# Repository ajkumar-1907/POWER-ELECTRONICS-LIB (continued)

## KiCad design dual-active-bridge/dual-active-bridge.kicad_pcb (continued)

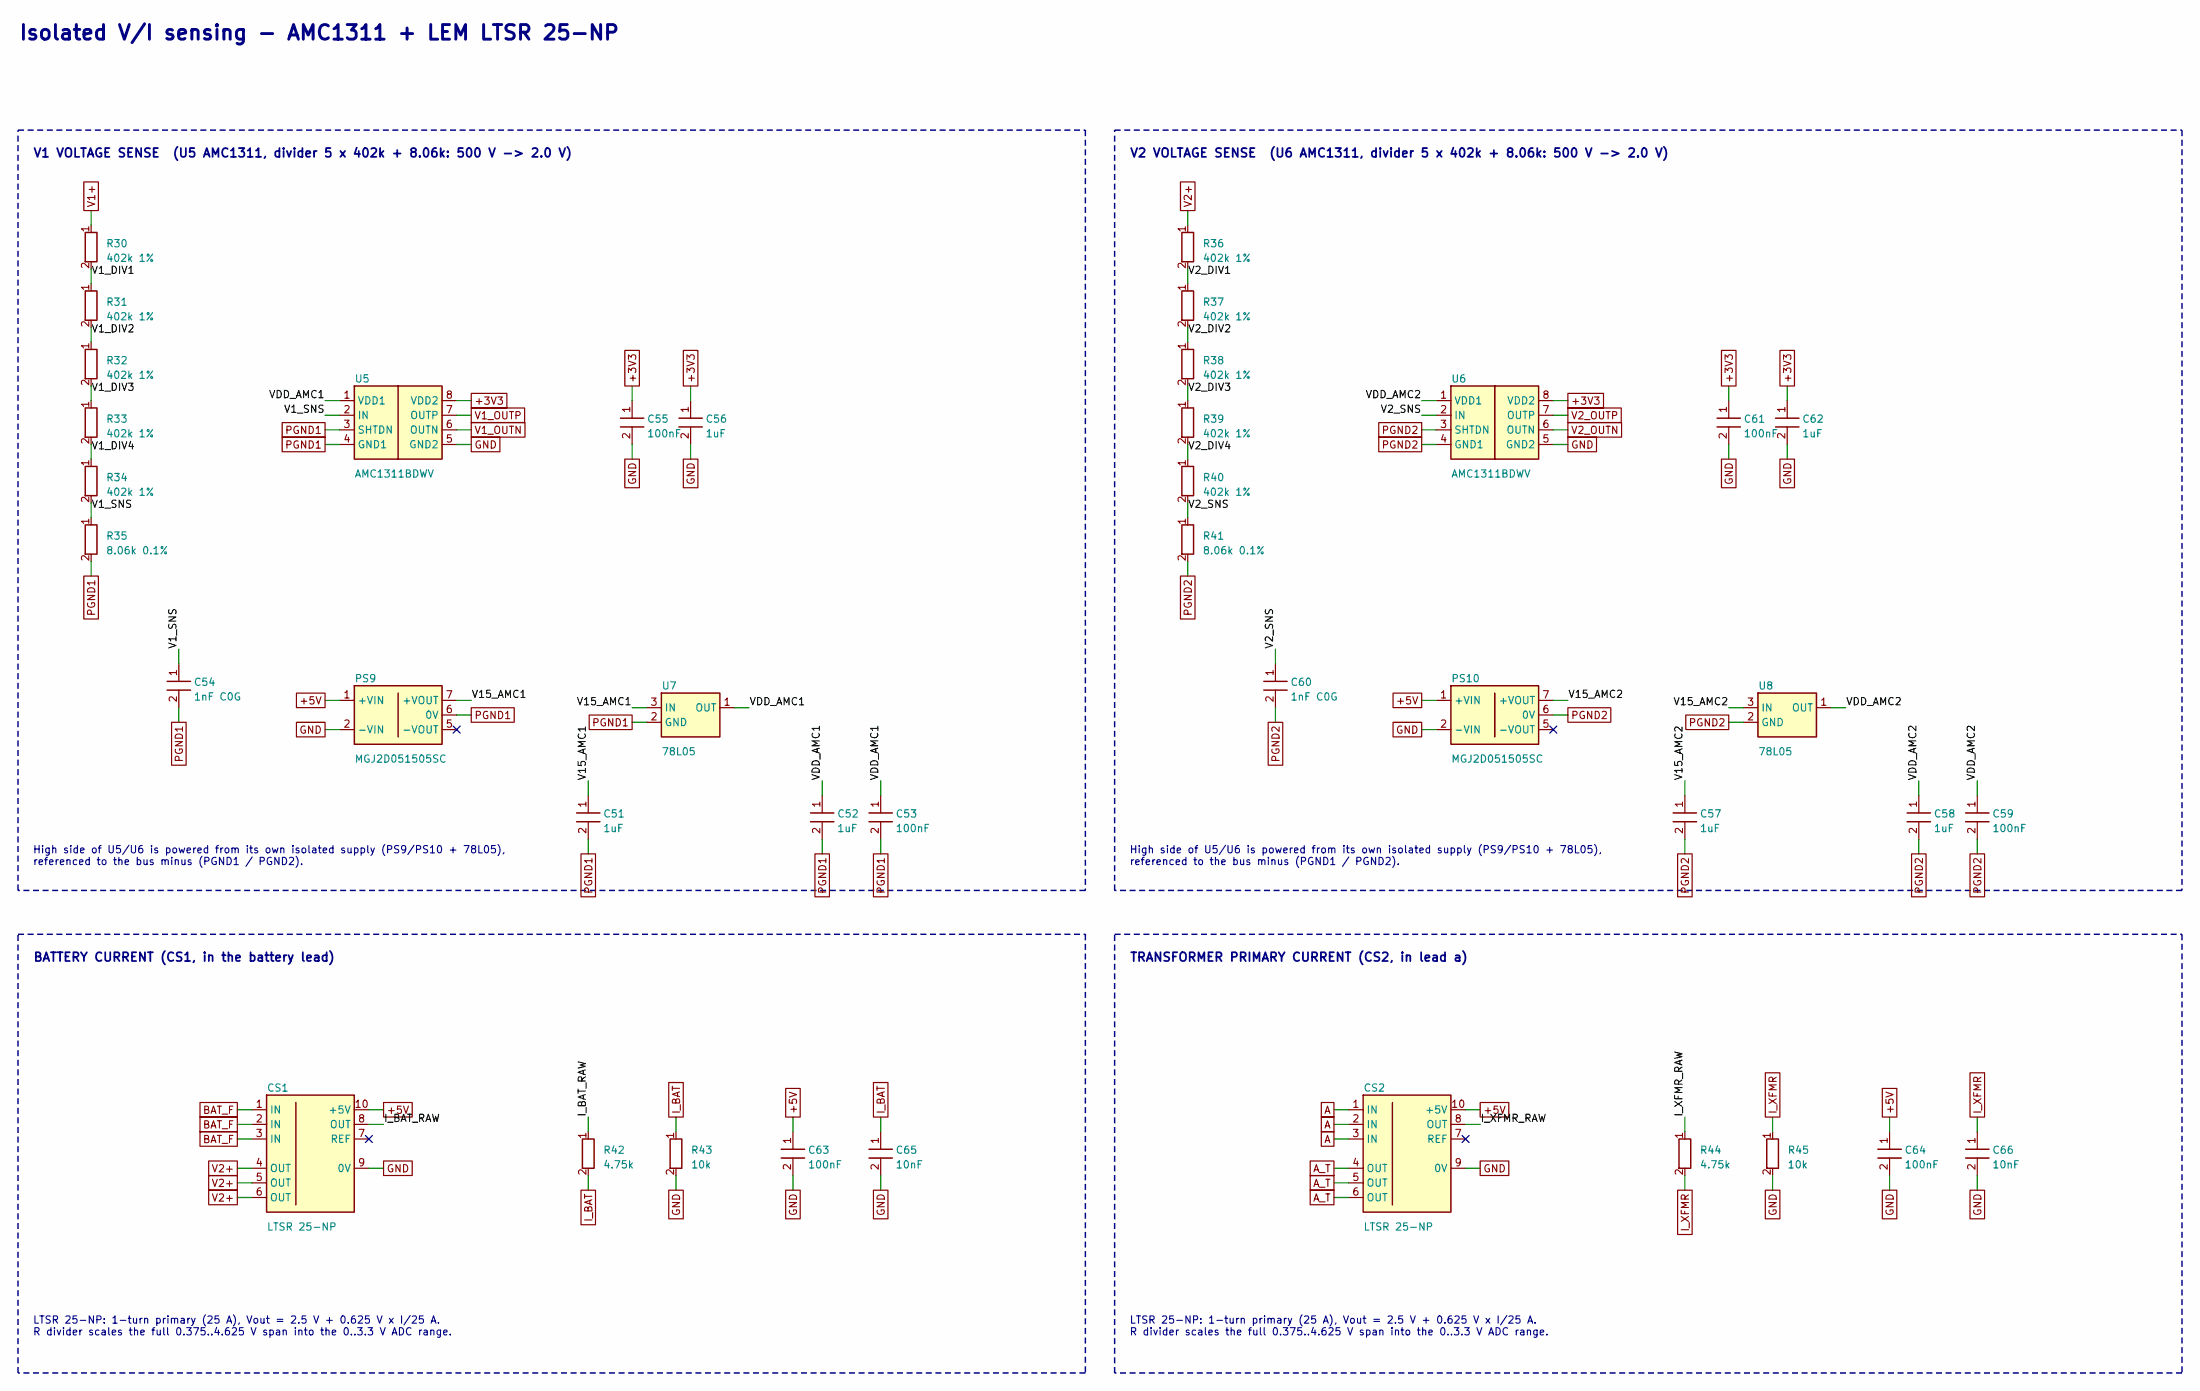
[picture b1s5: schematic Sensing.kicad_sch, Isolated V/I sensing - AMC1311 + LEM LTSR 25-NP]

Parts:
C51, C52, C56, C57, C58, C62: 1uF; C_0805_2012Metric
C53, C55, C59, C61, C63, C64: 100nF; C_0805_2012Metric
C54, C60: 1nF C0G; C_0805_2012Metric
C65, C66: 10nF; C_0805_2012Metric
CS1, CS2: LTSR 25-NP; LEM_LTSR-NP; MPN LEM LTSR 25-NP
PS9, PS10: MGJ2D051505SC; Converter_DCDC_Murata_MGJ2DxxxxxxSC_THT; MPN Murata MGJ2D051505SC
R30, R31, R32, R33, R34, R36, R37, R38, R39, R40: 402k 1%; R_1206_3216Metric
R35, R41: 8.06k 0.1%; R_1206_3216Metric
R42, R44: 4.75k; R_0805_2012Metric
R43, R45: 10k; R_0805_2012Metric
U5, U6: AMC1311BDWV; SOIC-8_7.5x5.85mm_P1.27mm; MPN TI AMC1311BDWV
U7, U8: 78L05; SOT-89-3; MPN ST L78L05ACUTR

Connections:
+3V3: C55.1, C56.1, C61.1, C62.1, U5.8 (VDD2), U6.8 (VDD2); also elsewhere on the board
+5V: C63.1, C64.1, CS1.10 (+5V), CS2.10 (+5V), PS9.1 (+VIN), PS10.1 (+VIN); also elsewhere on the board
/Sensing/I_BAT_RAW: CS1.8 (OUT), R42.1
/Sensing/I_XFMR_RAW: CS2.8 (OUT), R44.1
/Sensing/V1_DIV1: R30.2, R31.1
/Sensing/V1_DIV2: R31.2, R32.1
/Sensing/V1_DIV3: R32.2, R33.1
/Sensing/V1_DIV4: R33.2, R34.1
/Sensing/V1_SNS: C54.1, R34.2, R35.1, U5.2 (IN)
/Sensing/V2_DIV1: R36.2, R37.1
/Sensing/V2_DIV2: R37.2, R38.1
/Sensing/V2_DIV3: R38.2, R39.1
/Sensing/V2_DIV4: R39.2, R40.1
/Sensing/V2_SNS: C60.1, R40.2, R41.1, U6.2 (IN)
/Sensing/V15_AMC1: C51.1, PS9.7 (+VOUT), U7.3 (IN)
/Sensing/V15_AMC2: C57.1, PS10.7 (+VOUT), U8.3 (IN)
/Sensing/VDD_AMC1: C52.1, C53.1, U5.1 (VDD1), U7.1 (OUT)
/Sensing/VDD_AMC2: C58.1, C59.1, U6.1 (VDD1), U8.1 (OUT)
A: CS2.1 (IN), CS2.2 (IN), CS2.3 (IN); also elsewhere on the board
A_T: CS2.4 (OUT), CS2.5 (OUT), CS2.6 (OUT); also elsewhere on the board
BAT_F: CS1.1 (IN), CS1.2 (IN), CS1.3 (IN); also elsewhere on the board
GND: C55.2, C56.2, C61.2, C62.2, C63.2, C64.2, C65.2, C66.2, CS1.9 (0V), CS2.9 (0V), PS9.2 (-VIN), PS10.2 (-VIN), R43.2, R45.2, U5.5 (GND2), U6.5 (GND2); also elsewhere on the board
I_BAT: C65.1, R42.2, R43.1; also elsewhere on the board
I_XFMR: C66.1, R44.2, R45.1; also elsewhere on the board
PGND1: C51.2, C52.2, C53.2, C54.2, PS9.6 (0V), R35.2, U5.3 (SHTDN), U5.4 (GND1), U7.2 (GND); also elsewhere on the board
PGND2: C57.2, C58.2, C59.2, C60.2, PS10.6 (0V), R41.2, U6.3 (SHTDN), U6.4 (GND1), U8.2 (GND); also elsewhere on the board
V1+: R30.1; also elsewhere on the board
V1_OUTN: U5.6 (OUTN); also elsewhere on the board
V1_OUTP: U5.7 (OUTP); also elsewhere on the board
V2+: CS1.4 (OUT), CS1.5 (OUT), CS1.6 (OUT), R36.1; also elsewhere on the board
V2_OUTN: U6.6 (OUTN); also elsewhere on the board
V2_OUTP: U6.7 (OUTP); also elsewhere on the board

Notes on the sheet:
High side of U5/U6 is powered from its own isolated supply (PS9/PS10 + 78L05), referenced to the bus minus (PGND1 / PGND2).
Isolated V/I sensing - AMC1311 + LEM LTSR 25-NP
LTSR 25-NP: 1-turn primary (25 A), Vout = 2.5 V + 0.625 V x I/25 A. R divider scales the full 0.375..4.625 V span into the 0..3.3 V ADC range.
TRANSFORMER PRIMARY CURRENT (CS2, in lead a)
BATTERY CURRENT (CS1, in the battery lead)
V1 VOLTAGE SENSE (U5 AMC1311, divider 5 x 402k + 8.06k: 500 V -> 2.0 V)
V2 VOLTAGE SENSE (U6 AMC1311, divider 5 x 402k + 8.06k: 500 V -> 2.0 V)

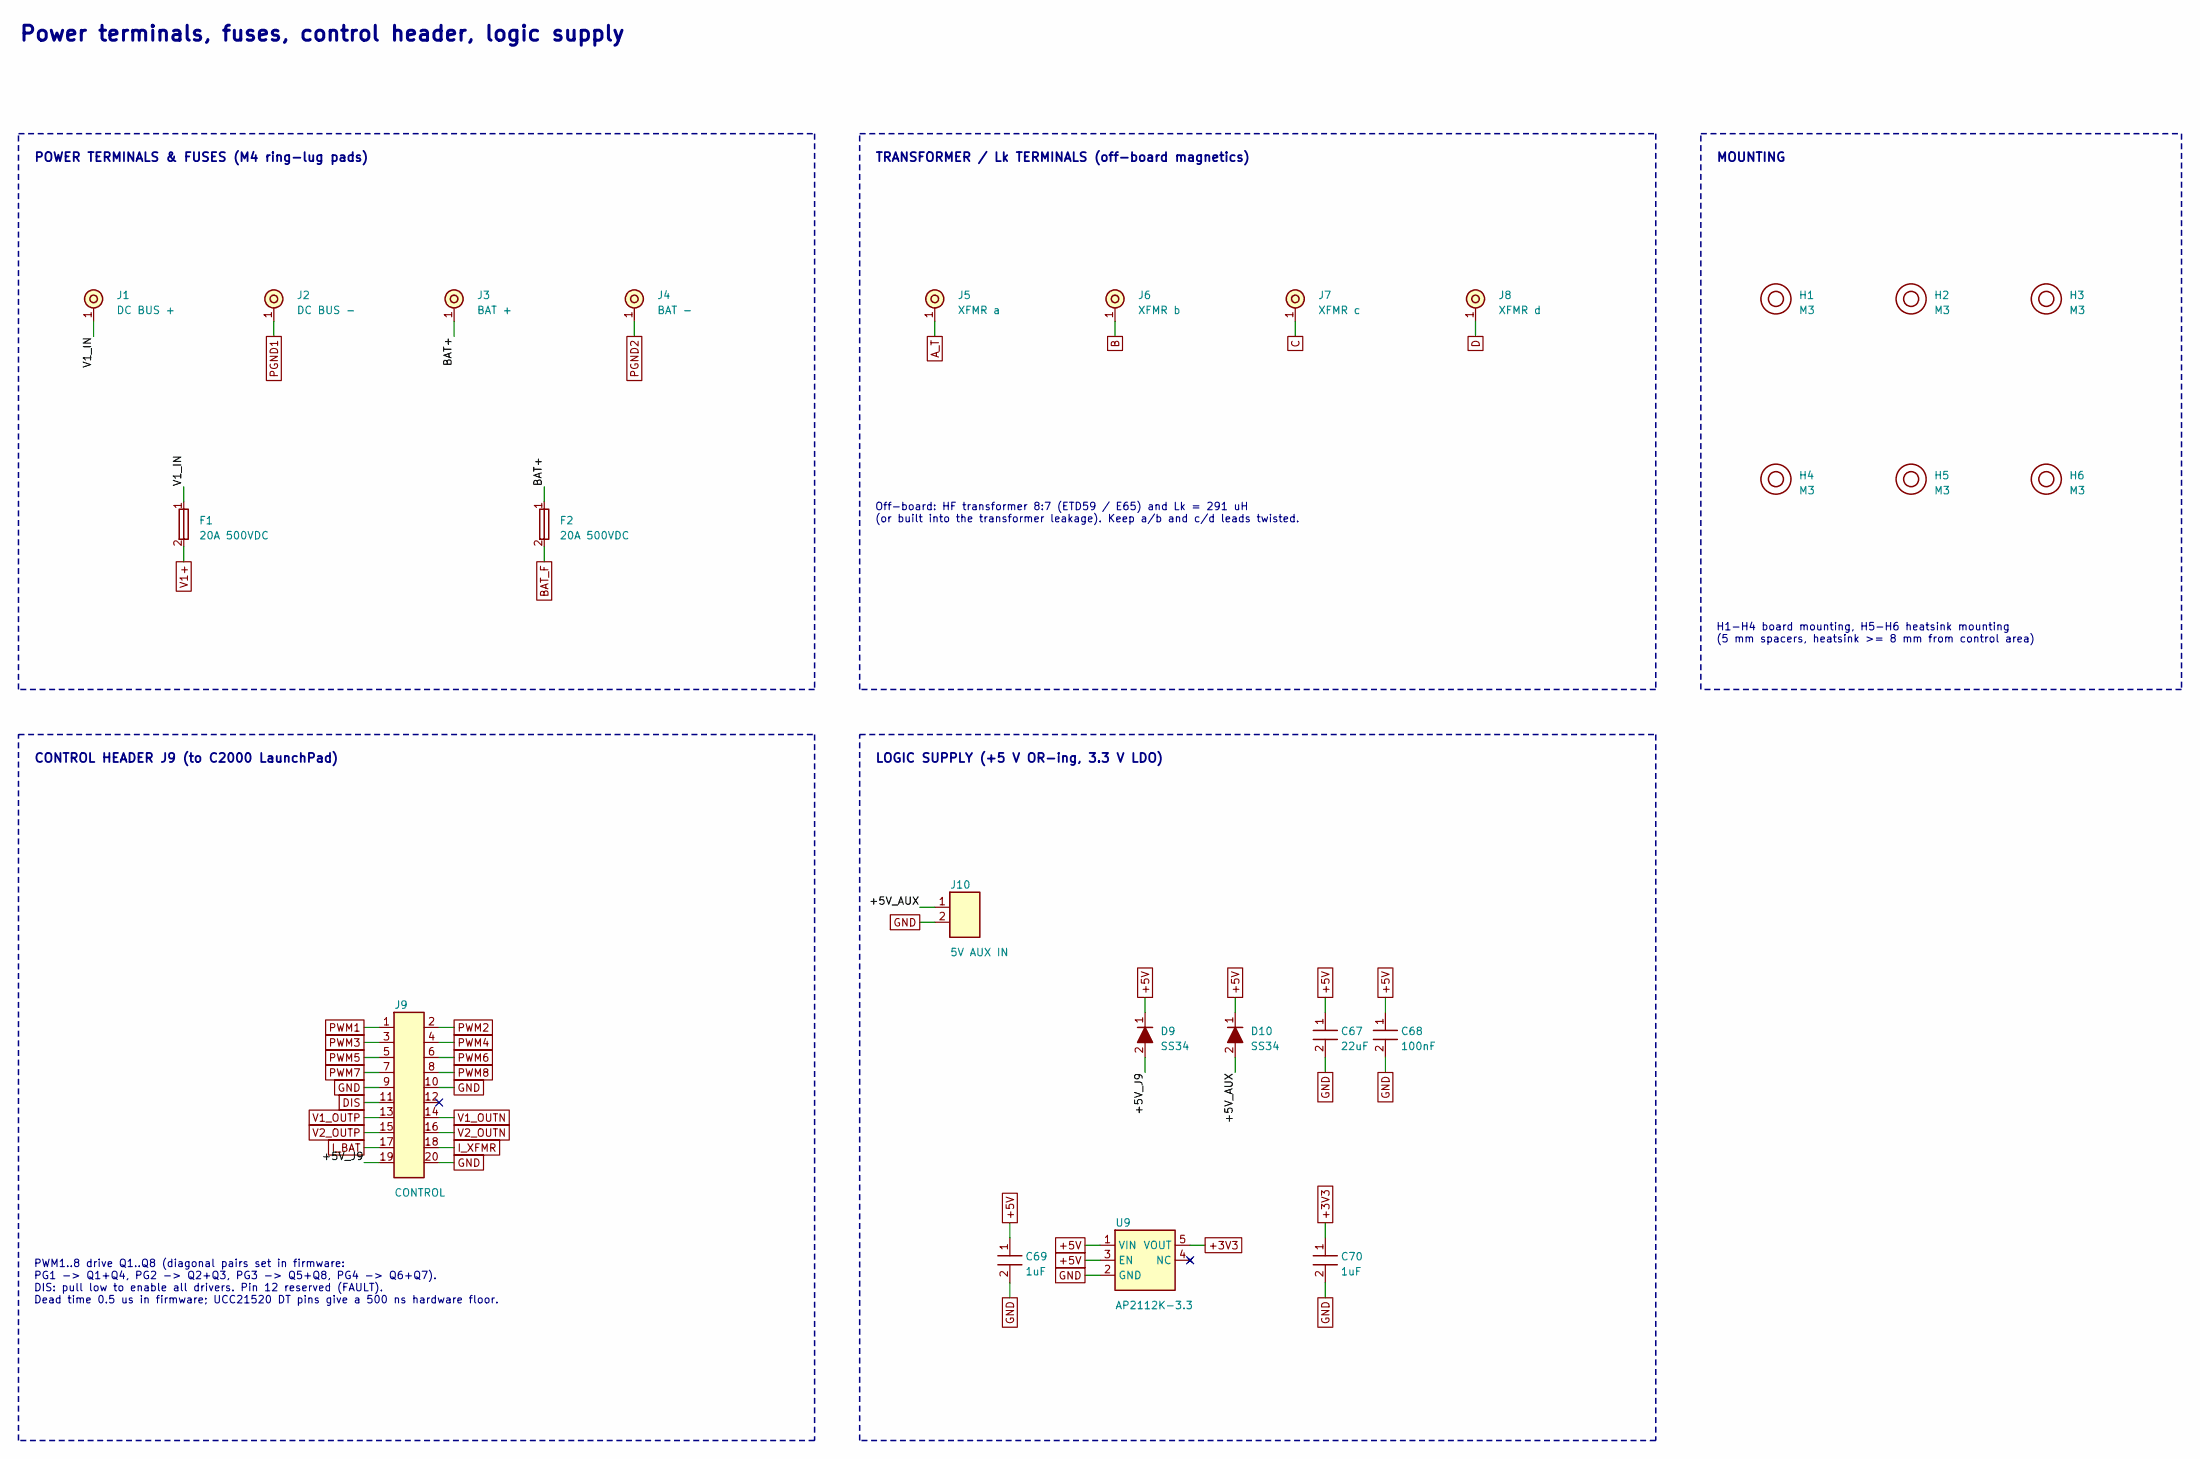
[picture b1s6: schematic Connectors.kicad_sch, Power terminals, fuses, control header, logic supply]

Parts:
C67: 22uF; C_1206_3216Metric
C68: 100nF; C_0805_2012Metric
C69, C70: 1uF; C_0805_2012Metric
D9, D10: SS34; D_SMA; MPN SS34
F1, F2: 20A 500VDC; Fuseholder_Clip-6.3x32mm_PCB; MPN Littelfuse 505 series 20 A
H1, H2, H3, H4, H5, H6: M3; MountingHole_3.2mm_M3
J1: DC BUS +; MountingHole_4.3mm_M4_Pad; MPN M4 ring lug
J2: DC BUS -; MountingHole_4.3mm_M4_Pad; MPN M4 ring lug
J3: BAT +; MountingHole_4.3mm_M4_Pad; MPN M4 ring lug
J4: BAT -; MountingHole_4.3mm_M4_Pad; MPN M4 ring lug
J5: XFMR a; MountingHole_4.3mm_M4_Pad; MPN M4 ring lug
J6: XFMR b; MountingHole_4.3mm_M4_Pad; MPN M4 ring lug
J7: XFMR c; MountingHole_4.3mm_M4_Pad; MPN M4 ring lug
J8: XFMR d; MountingHole_4.3mm_M4_Pad; MPN M4 ring lug
J9: CONTROL; PinHeader_2x10_P2.54mm_Vertical; MPN 2x10 2.54 mm header
J10: 5V AUX IN; TerminalBlock_Phoenix_MKDS-1,5-2-5.08_1x02_P5.08mm_Horizont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; MPN Phoenix MKDS 1,5/2-5,08
U9: AP2112K-3.3; SOT-23-5; MPN Diodes AP2112K-3.3TRG1

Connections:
+3V3: C70.1, U9.5 (VOUT); also elsewhere on the board
+5V: C67.1, C68.1, C69.1, D9.1 (K), D10.1 (K), U9.1 (VIN), U9.3 (EN); also elsewhere on the board
/Connectors/+5V_AUX: D10.2 (A), J10.1
/Connectors/+5V_J9: D9.2 (A), J9.19
/Connectors/BAT+: F2.1, J3.1
/Connectors/V1_IN: F1.1, J1.1
A_T: J5.1; also elsewhere on the board
B: J6.1; also elsewhere on the board
BAT_F: F2.2; also elsewhere on the board
C: J7.1; also elsewhere on the board
D: J8.1; also elsewhere on the board
DIS: J9.11; also elsewhere on the board
GND: C67.2, C68.2, C69.2, C70.2, J9.9, J9.10, J9.20, J10.2, U9.2 (GND); also elsewhere on the board
I_BAT: J9.17; also elsewhere on the board
I_XFMR: J9.18; also elsewhere on the board
PGND1: J2.1; also elsewhere on the board
PGND2: J4.1; also elsewhere on the board
PWM1: J9.1; also elsewhere on the board
PWM2: J9.2; also elsewhere on the board
PWM3: J9.3; also elsewhere on the board
PWM4: J9.4; also elsewhere on the board
PWM5: J9.5; also elsewhere on the board
PWM6: J9.6; also elsewhere on the board
PWM7: J9.7; also elsewhere on the board
PWM8: J9.8; also elsewhere on the board
V1+: F1.2; also elsewhere on the board
V1_OUTN: J9.14; also elsewhere on the board
V1_OUTP: J9.13; also elsewhere on the board
V2_OUTN: J9.16; also elsewhere on the board
V2_OUTP: J9.15; also elsewhere on the board

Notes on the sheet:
Off-board: HF transformer 8:7 (ETD59 / E65) and Lk = 291 uH (or built into the transformer leakage). Keep a/b and c/d leads twisted.
LOGIC SUPPLY (+5 V OR-ing, 3.3 V LDO)
Power terminals, fuses, control header, logic supply
MOUNTING
CONTROL HEADER J9 (to C2000 LaunchPad)
H1-H4 board mounting, H5-H6 heatsink mounting (5 mm spacers, heatsink >= 8 mm from control area)
PWM1..8 drive Q1..Q8 (diagonal pairs set in firmware: PG1 -> Q1+Q4, PG2 -> Q2+Q3, PG3 -> Q5+Q8, PG4 -> Q6+Q7). DIS: pull low to enable all drivers. Pin 12 reserved (FAULT). Dead time 0.5 us in firmware; UCC21520 DT pins give a 500 ns hardware floor.
TRANSFORMER / Lk TERMINALS (off-board magnetics)
POWER TERMINALS & FUSES (M4 ring-lug pads)

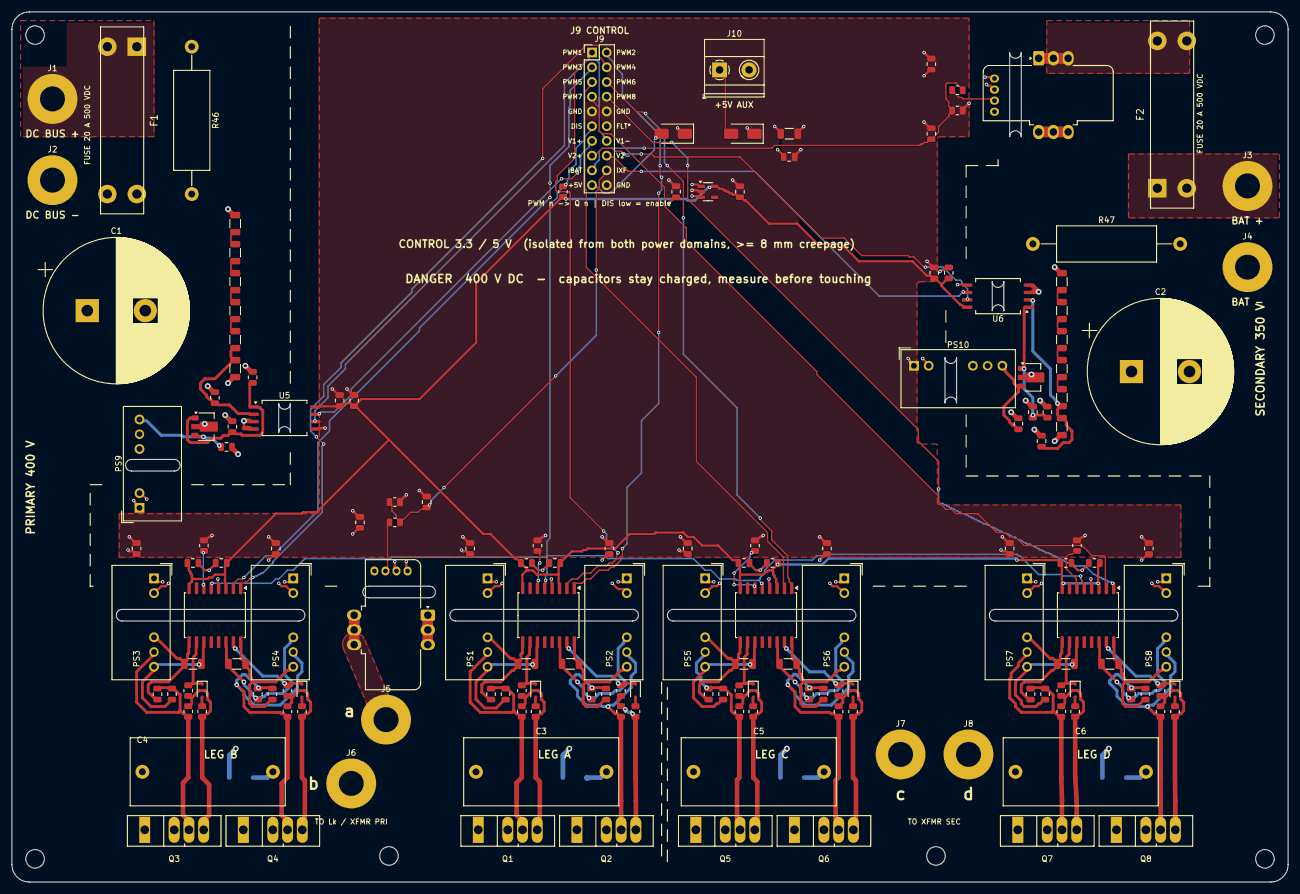
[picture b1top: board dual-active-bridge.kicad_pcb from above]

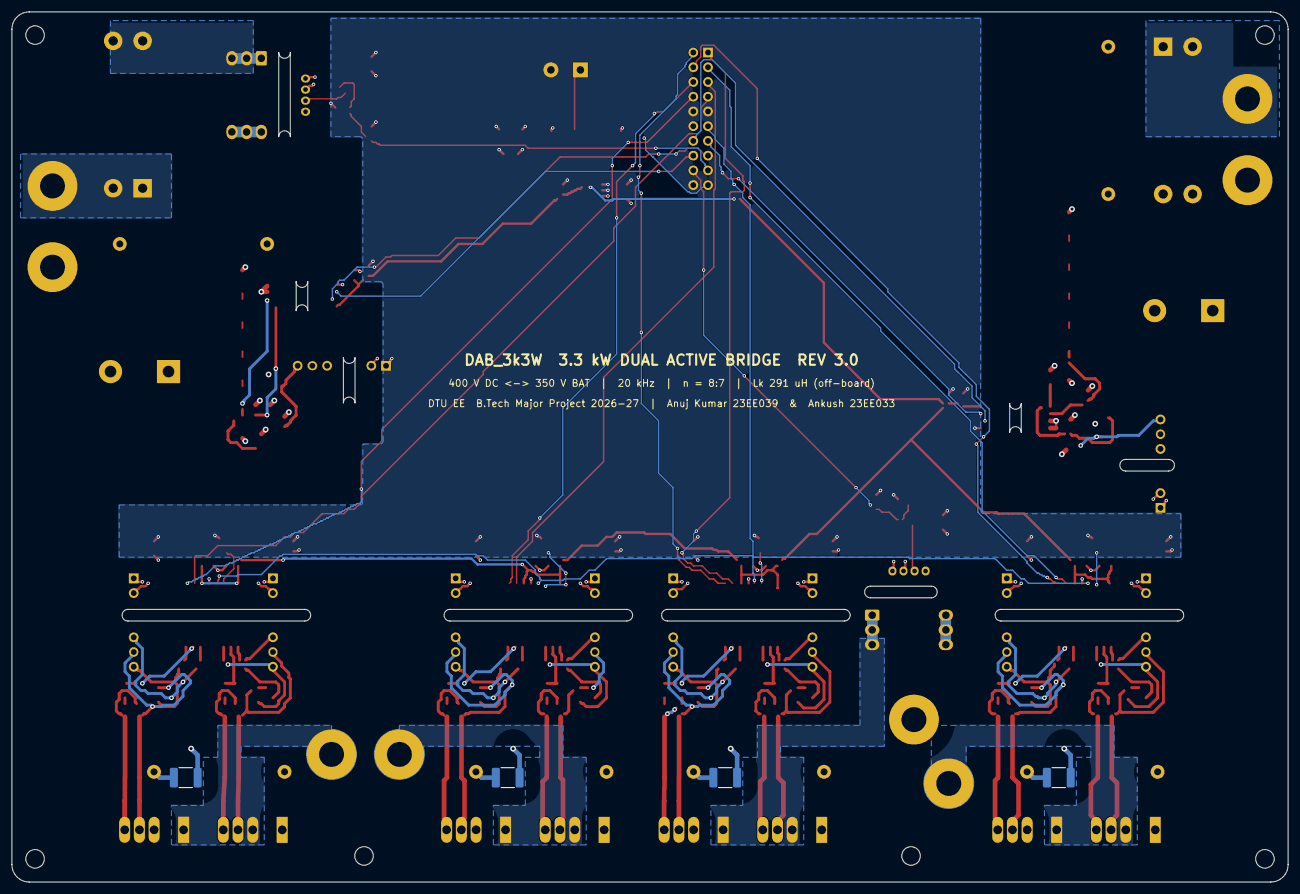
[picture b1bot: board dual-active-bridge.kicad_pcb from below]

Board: 4 copper layers, 220.0 x 150.0 mm, 174 parts (4 on the bottom side), 100 nets.

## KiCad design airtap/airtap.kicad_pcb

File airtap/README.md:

# AirTap: Touchless AC Switch

A touchless, proximity-triggered relay controller for **220 V AC** loads. Hold your hand 10–30 mm above the sensing area and a **VL53L0X time-of-flight sensor** detects it. The **ATmega328** then toggles an onboard relay to switch a lamp, fan or other mains appliance, with no physical contact.

> **Credit:** AirTap is a fork of **[ProxiWave-D (PWD-v010A)](https://github.com/ampnics/Proxiwave-D)** by **Ampnics**, released under the MIT License. The circuit, PCB layout and test firmware are Ampnics' original design. This fork re-brands the board silkscreen as "AIR-TAP", ports the project to KiCad 10, and adds Gerbers, renders and documentation. See [`NOTICE.md`](NOTICE.md).

> ⚠️ **DANGER: mains voltage.** The AC side of this board carries 220 V. Never touch it while it's powered, keep it in an enclosure, and only build it if you're experienced with mains wiring.

### 3D views

| Top | Bottom (sensor side) |
|---|---|
|  |  |

### Schematic sections

| 220 VAC → 5 VDC | AC connector, relay & buzzer |
|---|---|
|  |  |
| **ToF sensor** | **Microcontroller** |
|  |  |

### Layer views

| Front copper | Back copper |
|---|---|
|  |  |
| **Front silkscreen** | **Back silkscreen** |
|  |  |

## Overview

| Block | Parts | Function |
|---|---|---|
| **220 VAC → 5 VDC** | F1 fuse, RV1 MOV, C1, PS1 HLK-5M05, C3 | Fused, surge-protected isolated AC-DC module |
| **5 V → 3.3 V** | U2 AMS1117-3.3 + decoupling | Powers the MCU and sensor |
| **Microcontroller** | U3 ATmega328-A, Y1 8 MHz, SW1 reset | Reads the sensor, drives the relay, buzzer and LEDs |
| **ToF sensor** | U1 VL53L0X, I²C pull-ups | Measures hand distance (10–30 mm trigger window) |
| **Relay and buzzer** | K1 G5LE-1, Q1/Q2 AO3400A, D1 flyback, LS1 MLT-8530 | Switches the AC load; audible feedback |
| **Indicators** | D2 blue (relay), D3 red (power), D4 green (status) | Visual status |
| **Programming** | J2 2×3 ICSP | Flash with USBasp / AVRISP |
| **Backup sensor** | J3 3-pin | Optional IR proximity sensor input |

## Working Principle

1. **Power:** mains enters on J1 (LINE / NEUTRAL) through fuse F1 (0.5 A). MOV RV1 (10D561K) clamps surges, and the HLK-5M05 isolated module produces 5 V. The AMS1117 then makes 3.3 V for the ATmega328 and the VL53L0X.
2. **Sensing:** the VL53L0X sends out infrared laser pulses and measures their time of flight. The ATmega328 reads the distance over I²C (SDA = PC4, SCL = PC5).
3. **Decision:** when a hand is held inside the calibrated **10–30 mm** window, the firmware toggles the load state.
4. **Switching:** PC2 drives Q1 (AO3400A logic-level MOSFET), which energises relay K1. D1 clamps the coil's flyback spike. The relay's NO / C / NC contacts are brought out on J1.
5. **Feedback:** PC3 drives the buzzer through Q2, the blue LED shows the relay state, and the green LED (PC1) shows status.

## GPIO Mapping

| ATmega328 Pin | Signal | Function |
|---|---|---|
| PC1 / A1 | STS | Relay status LED |
| PC2 / A2 | RLY | Relay driver (Q1) |
| PC3 / A3 | BUZZER | Buzzer driver (Q2) |
| PC4 / A4 | SDA | VL53L0X I²C data |
| PC5 / A5 | SCL | VL53L0X I²C clock |
| PD2 / D2 | XSHUT | VL53L0X shutdown / reset |
| PD4 / D4 | IR-BKP | Backup IR sensor (J3) |

## J1: AC Terminal (5-way)

| Pin | Label | Description |
|---|---|---|
| 1 | L/L | AC line (live) in |
| 2 | N | AC neutral in |
| 3 | NO | Relay normally-open |
| 4 | C | Relay common |
| 5 | NC | Relay normally-closed |

Wire the load between **NO** and neutral, and connect **C** to line, so the load is off until triggered.

## Key Equations

**ToF ranging:**
```
d = (c × t) / 2        c = 3×10⁸ m/s, t = round-trip time of the laser pulse
```

**Relay coil drive (G5LE-1, 5 V coil ≈ 72 Ω):**
```
I_coil ≈ 5 V / 72 Ω ≈ 70 mA      → switched by AO3400A (R_DS(on) ≈ 30 mΩ at V_GS = 2.5 V)
```

**LED current (3.3 V rail):**
```
I_LED = (3.3 − V_F) / R      e.g. (3.3 − 2.0) / 330 Ω ≈ 4 mA
```

## Specifications

| Parameter | Value |
|---|---|
| Input | 220 V AC, 50 Hz |
| Load Switching | SPDT relay (G5LE-1), NO / C / NC on screw terminal |
| Logic Supply | 5 V (HLK-5M05) → 3.3 V (AMS1117) |
| MCU | ATmega328-A @ 8 MHz, 3.3 V |
| Sensor | VL53L0X ToF, 10–30 mm calibrated trigger |
| Protection | 0.5 A fuse, 10D561K MOV, flyback diode |
| Programming | ICSP 2×3 |
| Board Size | 50 × 100 mm, 2-layer, 4 × M2.5 mounting holes, fiducials |

## Bill of Materials (key parts)

| Ref | Value | Package |
|---|---|---|
| PS1 | HLK-5M05 (220 VAC → 5 V) | Module |
| U3 | ATmega328-A | TQFP-32 |
| U1 | VL53L0CXV0DH1 (VL53L0X) | LGA |
| U2 | AMS1117-3.3 | SOT-223 |
| K1 | Omron G5LE-1 relay, 5 V coil | THT |
| Q1, Q2 | AO3400A N-MOSFET | SOT-23 |
| D1 | 1N4148W | SOD-123 |
| F1 | 0.5 A / 250 VAC fuse | Littelfuse 395 |
| RV1 | 10D561K MOV | Disc 12 mm |
| C1 | 0.1 µF X2 film | 13 × 6 mm |
| C3 | 220 µF electrolytic | 8 × 10 mm |
| LS1 | MLT-8530 buzzer | SMD |
| Y1 | 8 MHz resonator | SMD 3-pin |
| J1 | 5-way screw terminal, 5.08 mm | THT |

Plus 0603 resistors, capacitors and LEDs; see the schematic for full values.

## Firmware

Test sketches by the original author are in [`firmware/test-codes/`](firmware/test-codes/):

| Sketch | Tests |
|---|---|
| `ToF-Sensor` | VL53L0X I²C ranging (prints distance over UART) |
| `Relay` | Relay coil driver and flyback diode |
| `Relay-Led` | Relay status LED |
| `Buzzer` | Buzzer driver |

**Setup:** in the Arduino IDE, install **MiniCore** (board manager URL `https://raw.githubusercontent.com/MCUdude/MiniCore/master/package_MCUdude_MiniCore_index.json`), then choose *ATmega328, External 8 MHz, 3.3 V*. Install the **VL53L0X** library by Pololu, and flash through J2 with a USBasp.

## Design Notes

- **J3 footprint:** the backup IR connector (J3) has no footprint assigned in the schematic, although the PCB has one. Assign it, for example `PinHeader_1x03_P2.54mm`, before running "Update PCB from Schematic", or KiCad will flag it.
- **Isolation:** the AC/DC boundary is marked on the silkscreen. For extra safety, consider adding a routed isolation slot between the mains section and the logic section.
- **C1** must be an **X2-rated** safety capacitor.
- **Load rating:** the relay is rated 10 A, but the fuse (0.5 A) protects the logic supply only. Fuse the load circuit separately, sized for your appliance.
- **3D models:** the vendor 3D models (relay, buzzer, terminal, switch) aren't included, so KiCad's 3D viewer shows those parts without a body. The 3D renders in this folder were made with them.

## Files in This Folder

| File | Description |
|---|---|
| `airtap.kicad_pro` / `.kicad_sch` / `.kicad_pcb` | KiCad 10 project, schematic and PCB |
| `airtap-PTH.drl` / `airtap-NPTH.drl` | Drill files |
| `gerbers/` | Gerber set for fabrication (incl. paste layers) |
| `firmware/test-codes/` | Arduino test sketches (original author) |
| `schematic.png` | Full schematic image |
| `schematic-*.png` | Schematic section close-ups |
| `pcb-3d-top.png` / `pcb-3d-bottom.png` / `pcb-3d-angle.png` | 3D renders |
| `pcb-layout2.png` / `pcb-layout.png` | Layout previews |
| `pcb-front-copper.png` / `pcb-back-copper.png` | Copper layer views |
| `pcb-front-silkscreen.png` / `pcb-back-silkscreen.png` | Silkscreen layer views |
| `NOTICE.md` | Original copyright and license notice |

## How to Use

1. Open `airtap.kicad_pro` in [KiCad](https://www.kicad.org/) 10 or later.
2. To manufacture, zip `gerbers/` together with the two `.drl` files and upload them to any PCB fab.
3. After assembly, flash the test sketches through J2 to check each block, then load your main firmware.
4. Calibrate the trigger distance (10–30 mm) for your enclosure.

## License

The original ProxiWave-D design is © Ampnics, released under the MIT License (see [`NOTICE.md`](NOTICE.md)). Changes in this fork are released under the repository's [MIT License](../LICENSE).

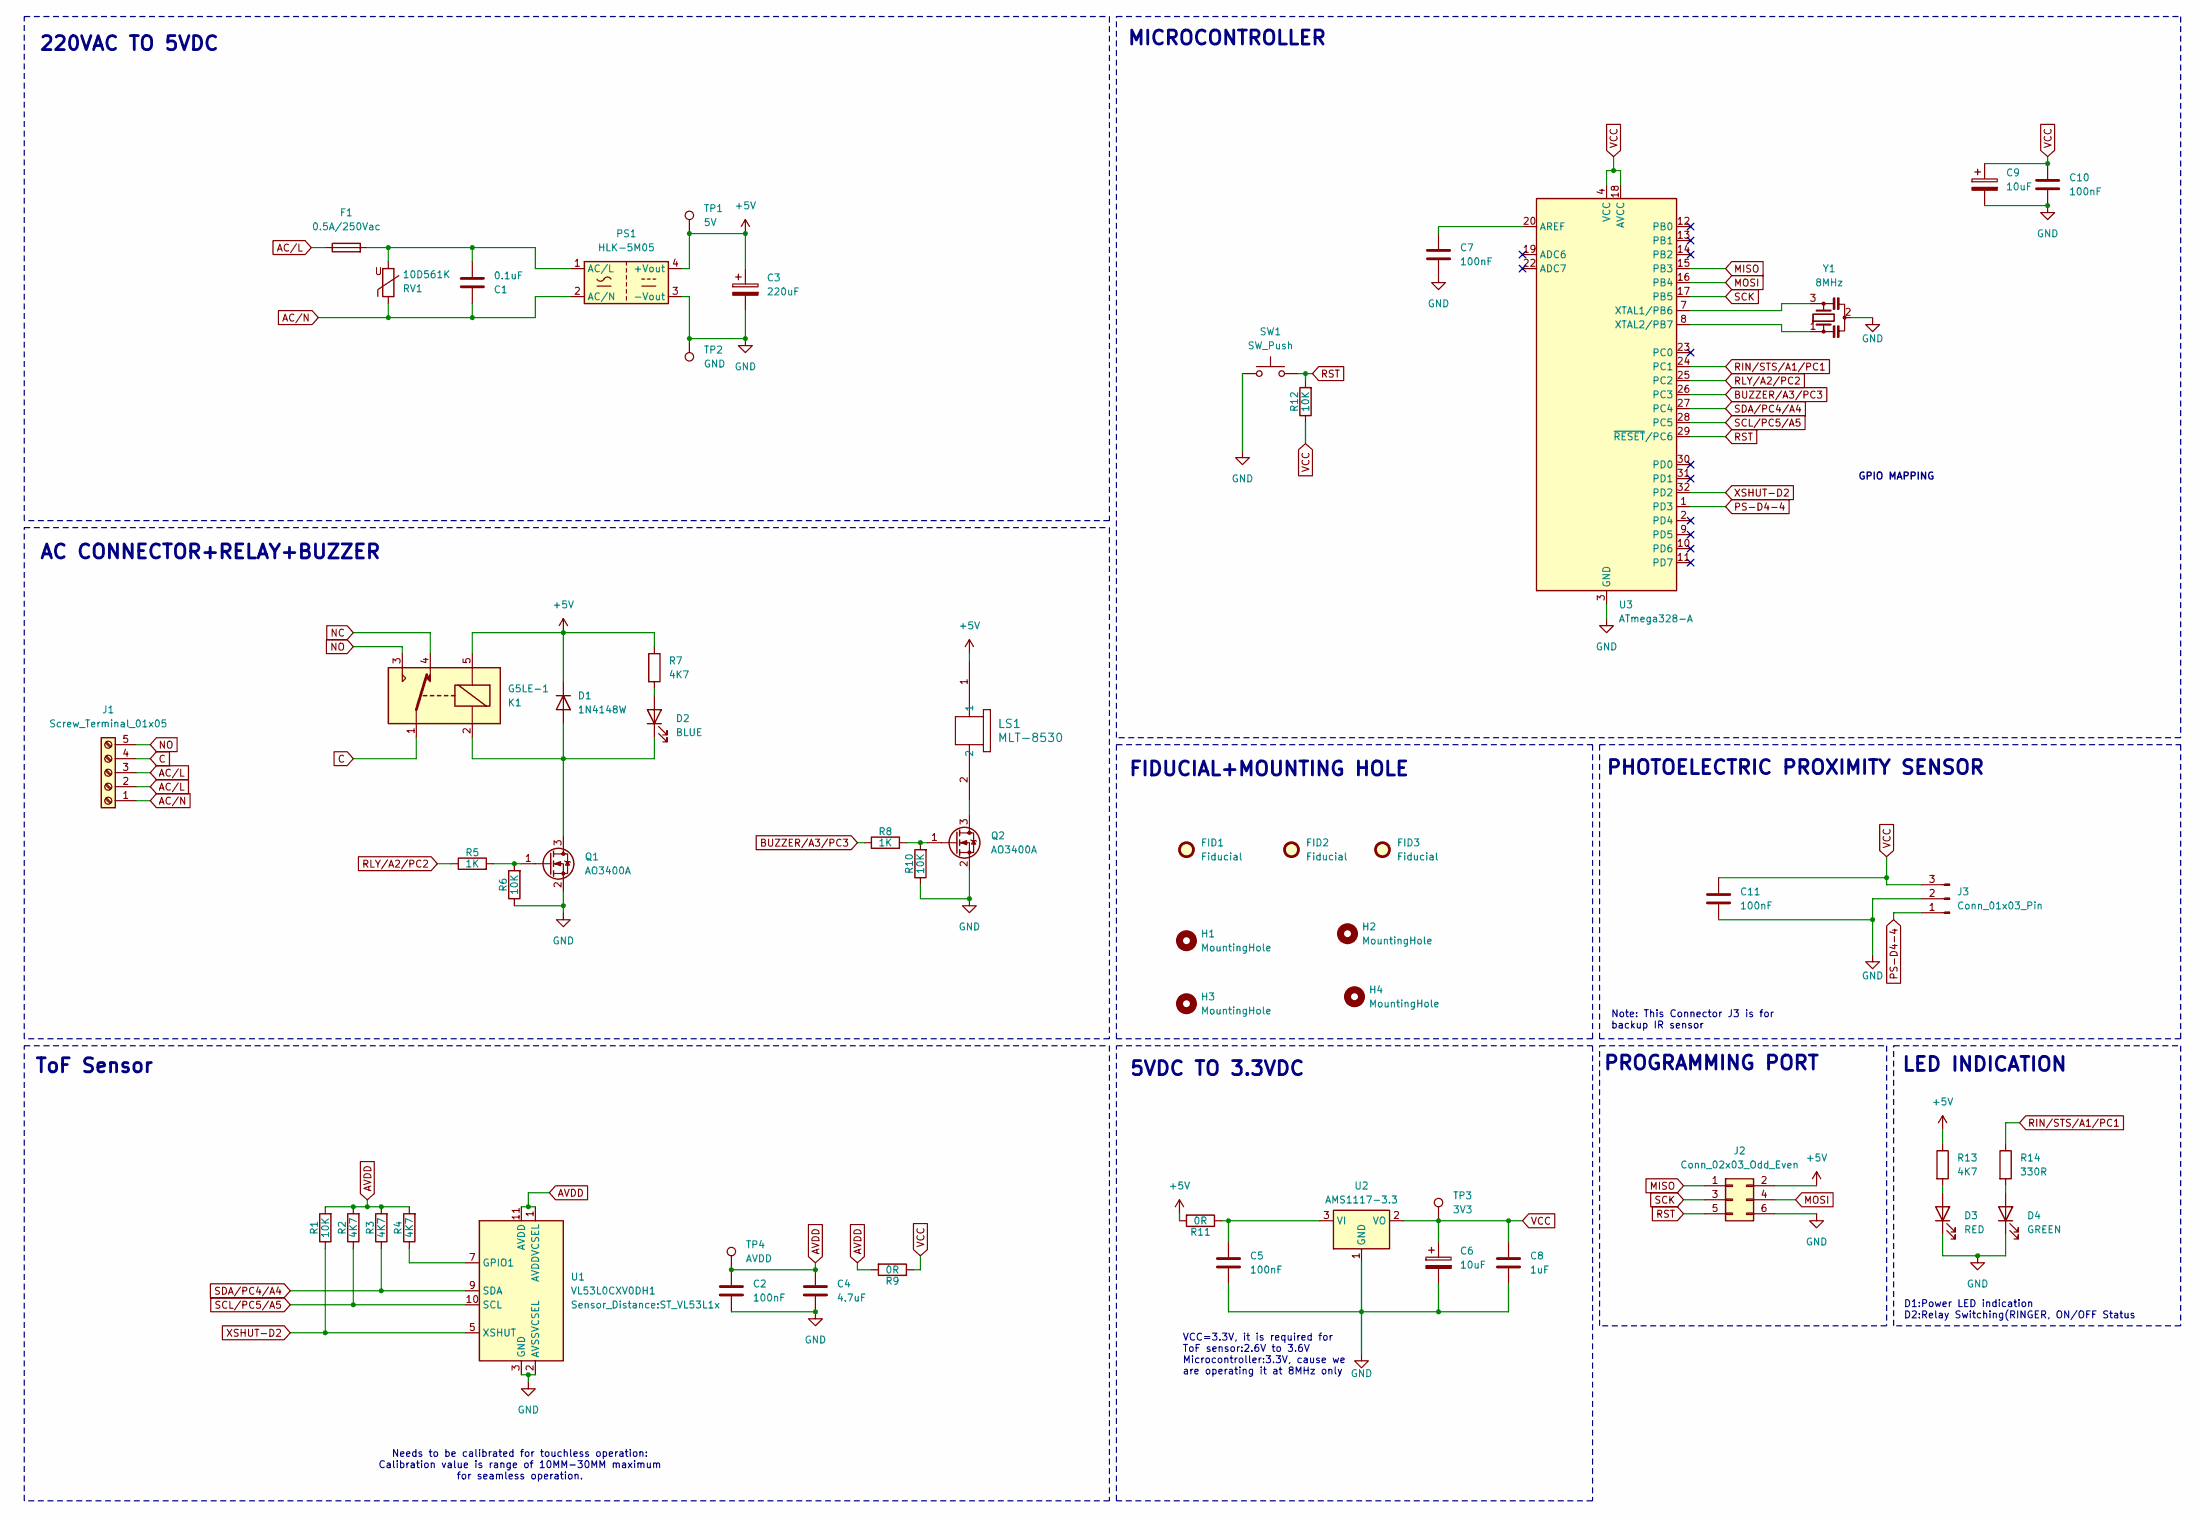
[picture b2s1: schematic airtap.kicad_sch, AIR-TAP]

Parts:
C1: 0.1uF; C_Rect_L13.0mm_W6.0mm_P10.00mm_FKS3_FKP3_MKS4
C2, C5, C7, C10, C11: 100nF; C_0603_1608Metric
C3: 220uF; CP_Elec_8x10
C4: 4.7uF; C_0603_1608Metric
C6, C9: 10uF; CP_EIA-3216-18_Kemet-A
C8: 1uF; C_0603_1608Metric
D1: 1N4148W; D_SOD-123
D2: BLUE; LED_0603_1608Metric
D3: RED; LED_0603_1608Metric
D4: GREEN; LED_0603_1608Metric
F1: 0.5A/250Vac; Fuse_Littelfuse_395Series
FID1, FID2, FID3: Fiducial; Fiducial_0.75mm_Mask1.5mm
H1, H2, H3, H4: MountingHole; MountingHole_2.7mm
J1: Screw_Terminal_01x05; TerminalBlock_bornier-5_P5.08mm
J2: Conn_02x03_Odd_Even; PinHeader_2x03_P2.54mm_Vertical
J3: Conn_01x03_Pin; MPN B3B-XH-A
K1: G5LE-1; Relay_SPDT_Omron-G5LE-1
LS1: MLT-8530; MLT-8530_JHE
PS1: HLK-5M05; Converter_ACDC_Hi-Link_HLK-5Mxx
Q1, Q2: AO3400A; SOT-23
R1, R6, R10, R12: 10K; R_0603_1608Metric
R2, R3, R4, R7, R13: 4K7; R_0603_1608Metric
R5, R8: 1K; R_0603_1608Metric
R9, R11: 0R; R_0603_1608Metric
R14: 330R; R_0603_1608Metric
RV1: 10D561K; RV_Disc_D12mm_W5.8mm_P7.5mm
SW1: SW_Push; SW_Tactile_SKHH_Angled
TP1: 5V; TestPoint_Pad_D1.5mm
TP2: GND; TestPoint_Pad_D1.5mm
TP3: 3V3; TestPoint_Pad_D1.5mm
TP4: AVDD; TestPoint_Pad_D1.5mm
U1: VL53L0CXV0DH1; ST_VL53L1x
U2: AMS1117-3.3; SOT-223-3_TabPin2
U3: ATmega328-A; TQFP-32_7x7mm_P0.8mm
Y1: 8MHz; Resonator_SMD_Murata_CSTxExxV-3Pin_3.0x1.1mm

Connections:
+5V: C3.1, D1.1 (K), J2.2, K1.5, LS1.1, PS1.4 (+Vout), R7.1, R11.2, R13.1, TP1.1
AC/L: F1.1, J1.2, J1.3
AC/N: C1.1, J1.1, PS1.2 (AC/N), RV1.1
AVDD: C2.1, C4.1, R1.2, R2.2, R3.2, R4.2, R9.2, TP4.1, U1.1 (AVDDVCSEL), U1.11 (AVDD)
BUZZER/A3/PC3: R8.1, U3.26 (PC3)
C: J1.4, K1.1
GND: C2.2, C3.2, C4.2, C5.2, C6.2, C7.2, C8.2, C9.2, C10.2, C11.2, D3.1 (K), D4.1 (K), J2.6, J3.2, PS1.3 (-Vout), Q1.2 (S), Q2.2 (S), R6.1, R10.1, SW1.1, TP2.1, U1.2 (AVSSVCSEL), U1.3 (GND), U1.4 (GND), U1.6 (GND), U1.12 (GND), U2.1 (GND), U3.3 (GND), U3.5 (GND), U3.21 (GND), Y1.2
MISO: J2.1, U3.15 (PB3)
MOSI: J2.4, U3.16 (PB4)
NC: K1.4
NO: J1.5, K1.3
unnamed: D1.2 (A), D2.1 (K), K1.2, Q1.3 (D)
unnamed: D2.2 (A), R7.2
unnamed: D3.2 (A), R13.2
unnamed: D4.2 (A), R14.2
unnamed: C1.2, F1.2, PS1.1 (AC/L), RV1.2
unnamed: Q1.1 (G), R5.2, R6.2
unnamed: LS1.2, Q2.3 (D)
unnamed: Q2.1 (G), R8.2, R10.2
unnamed: R4.1, U1.7 (GPIO1)
unnamed: C5.1, R11.1, U2.3 (VI)
unnamed: C7.1, U3.20 (AREF)
unnamed: U3.7 (XTAL1/PB6), Y1.3
unnamed: U3.8 (XTAL2/PB7), Y1.1
PS-D4-4: J3.1, U3.1 (PD3)
RIN/STS/A1/PC1: R14.1, U3.24 (PC1)
RLY/A2/PC2: R5.1, U3.25 (PC2)
RST: J2.5, R12.2, SW1.2, U3.29 (~RESET/PC6)
SCK: J2.3, U3.17 (PB5)
SCL/PC5/A5: R2.1, U1.10 (SCL), U3.28 (PC5)
SDA/PC4/A4: R3.1, U1.9 (SDA), U3.27 (PC4)
VCC: C6.1, C8.1, C9.1, C10.1, C11.1, J3.3, R9.1, R12.1, TP3.1, U2.2 (VO), U3.4 (VCC), U3.6 (VCC), U3.18 (AVCC)
XSHUT-D2: R1.1, U1.5 (XSHUT), U3.32 (PD2)

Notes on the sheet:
VCC=3.3V, it is required for ToF sensor:2.6V to 3.6V Microcontroller:3.3V, cause we are operating it at 8MHz only
220VAC TO 5VDC
ToF Sensor
PHOTOELECTRIC PROXIMITY SENSOR
MICROCONTROLLER
5VDC TO 3.3VDC
Note: This Connector J3 is for backup IR sensor
GPIO MAPPING
PROGRAMMING PORT
AC CONNECTOR+RELAY+BUZZER
LED INDICATION
FIDUCIAL+MOUNTING HOLE
D1:Power LED indication D2:Relay Switching(RINGER, ON/OFF Status
Needs to be calibrated for touchless operation: Calibration value is range of 10MM-30MM maximum for seamless operation.

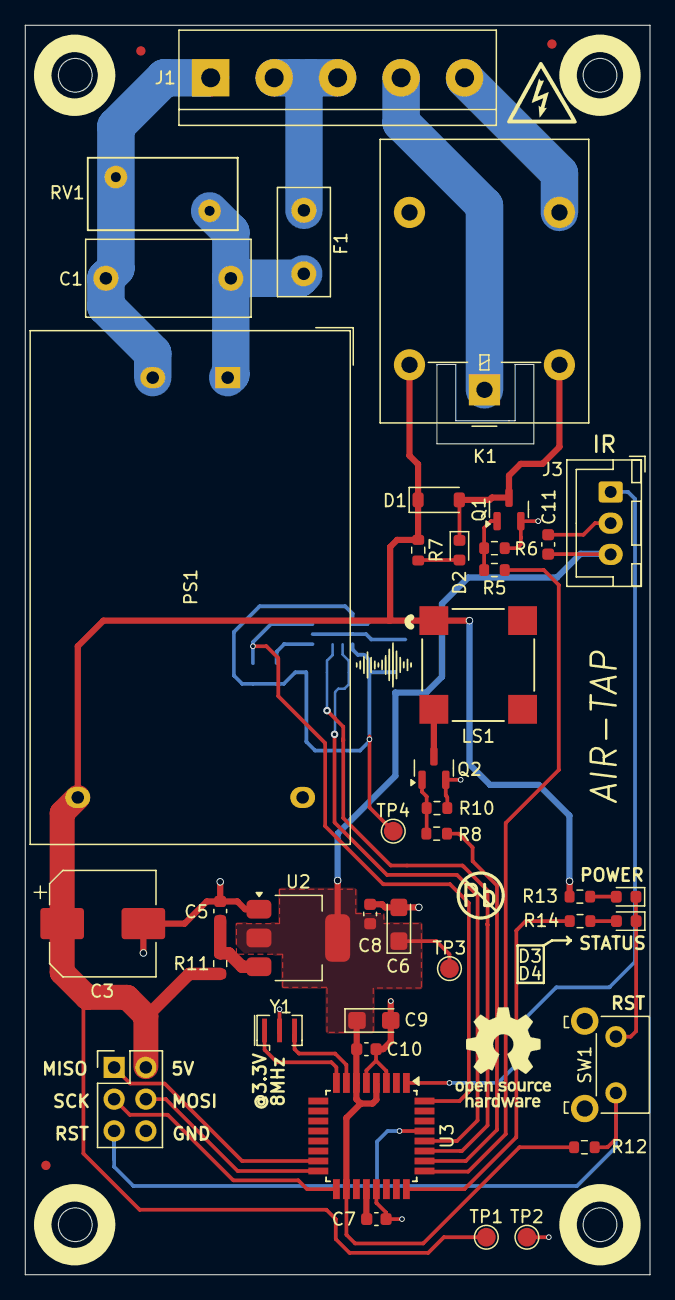
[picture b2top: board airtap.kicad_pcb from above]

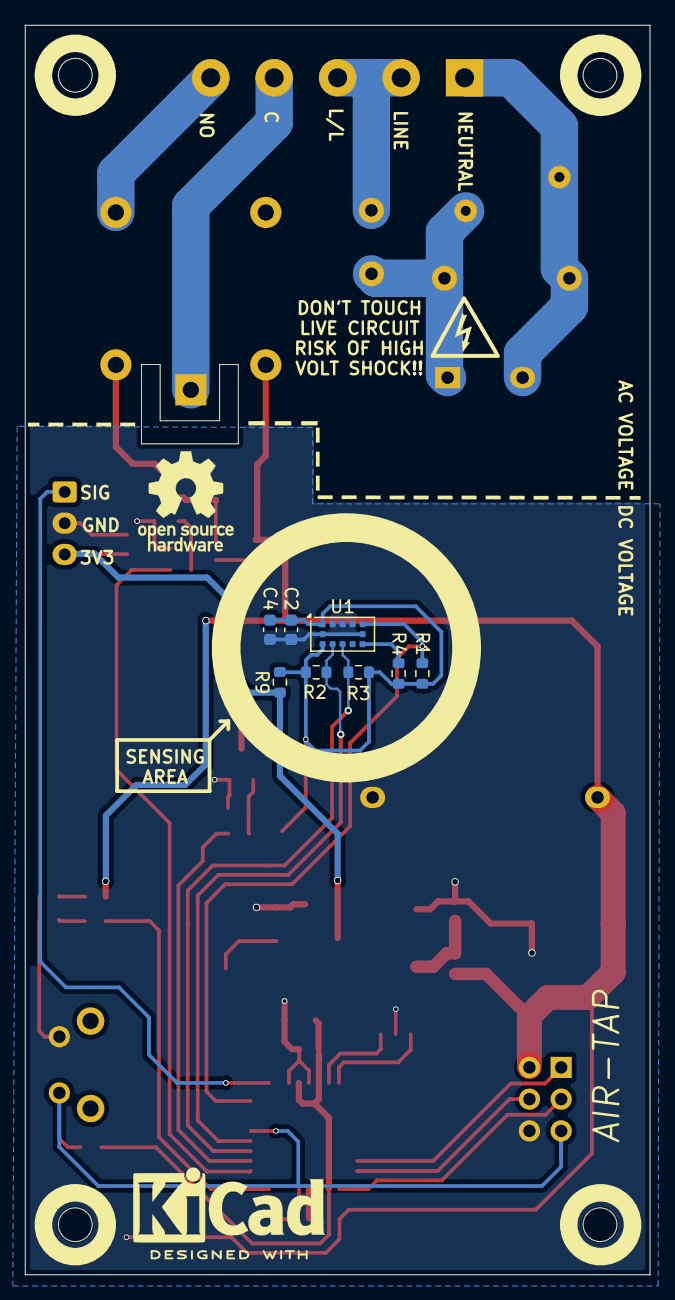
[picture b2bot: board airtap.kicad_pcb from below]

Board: 2 copper layers, 50.0 x 100.0 mm, 56 parts (8 on the bottom side), 32 nets.

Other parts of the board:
Sign-PbFree: LOGO_PBFREE
